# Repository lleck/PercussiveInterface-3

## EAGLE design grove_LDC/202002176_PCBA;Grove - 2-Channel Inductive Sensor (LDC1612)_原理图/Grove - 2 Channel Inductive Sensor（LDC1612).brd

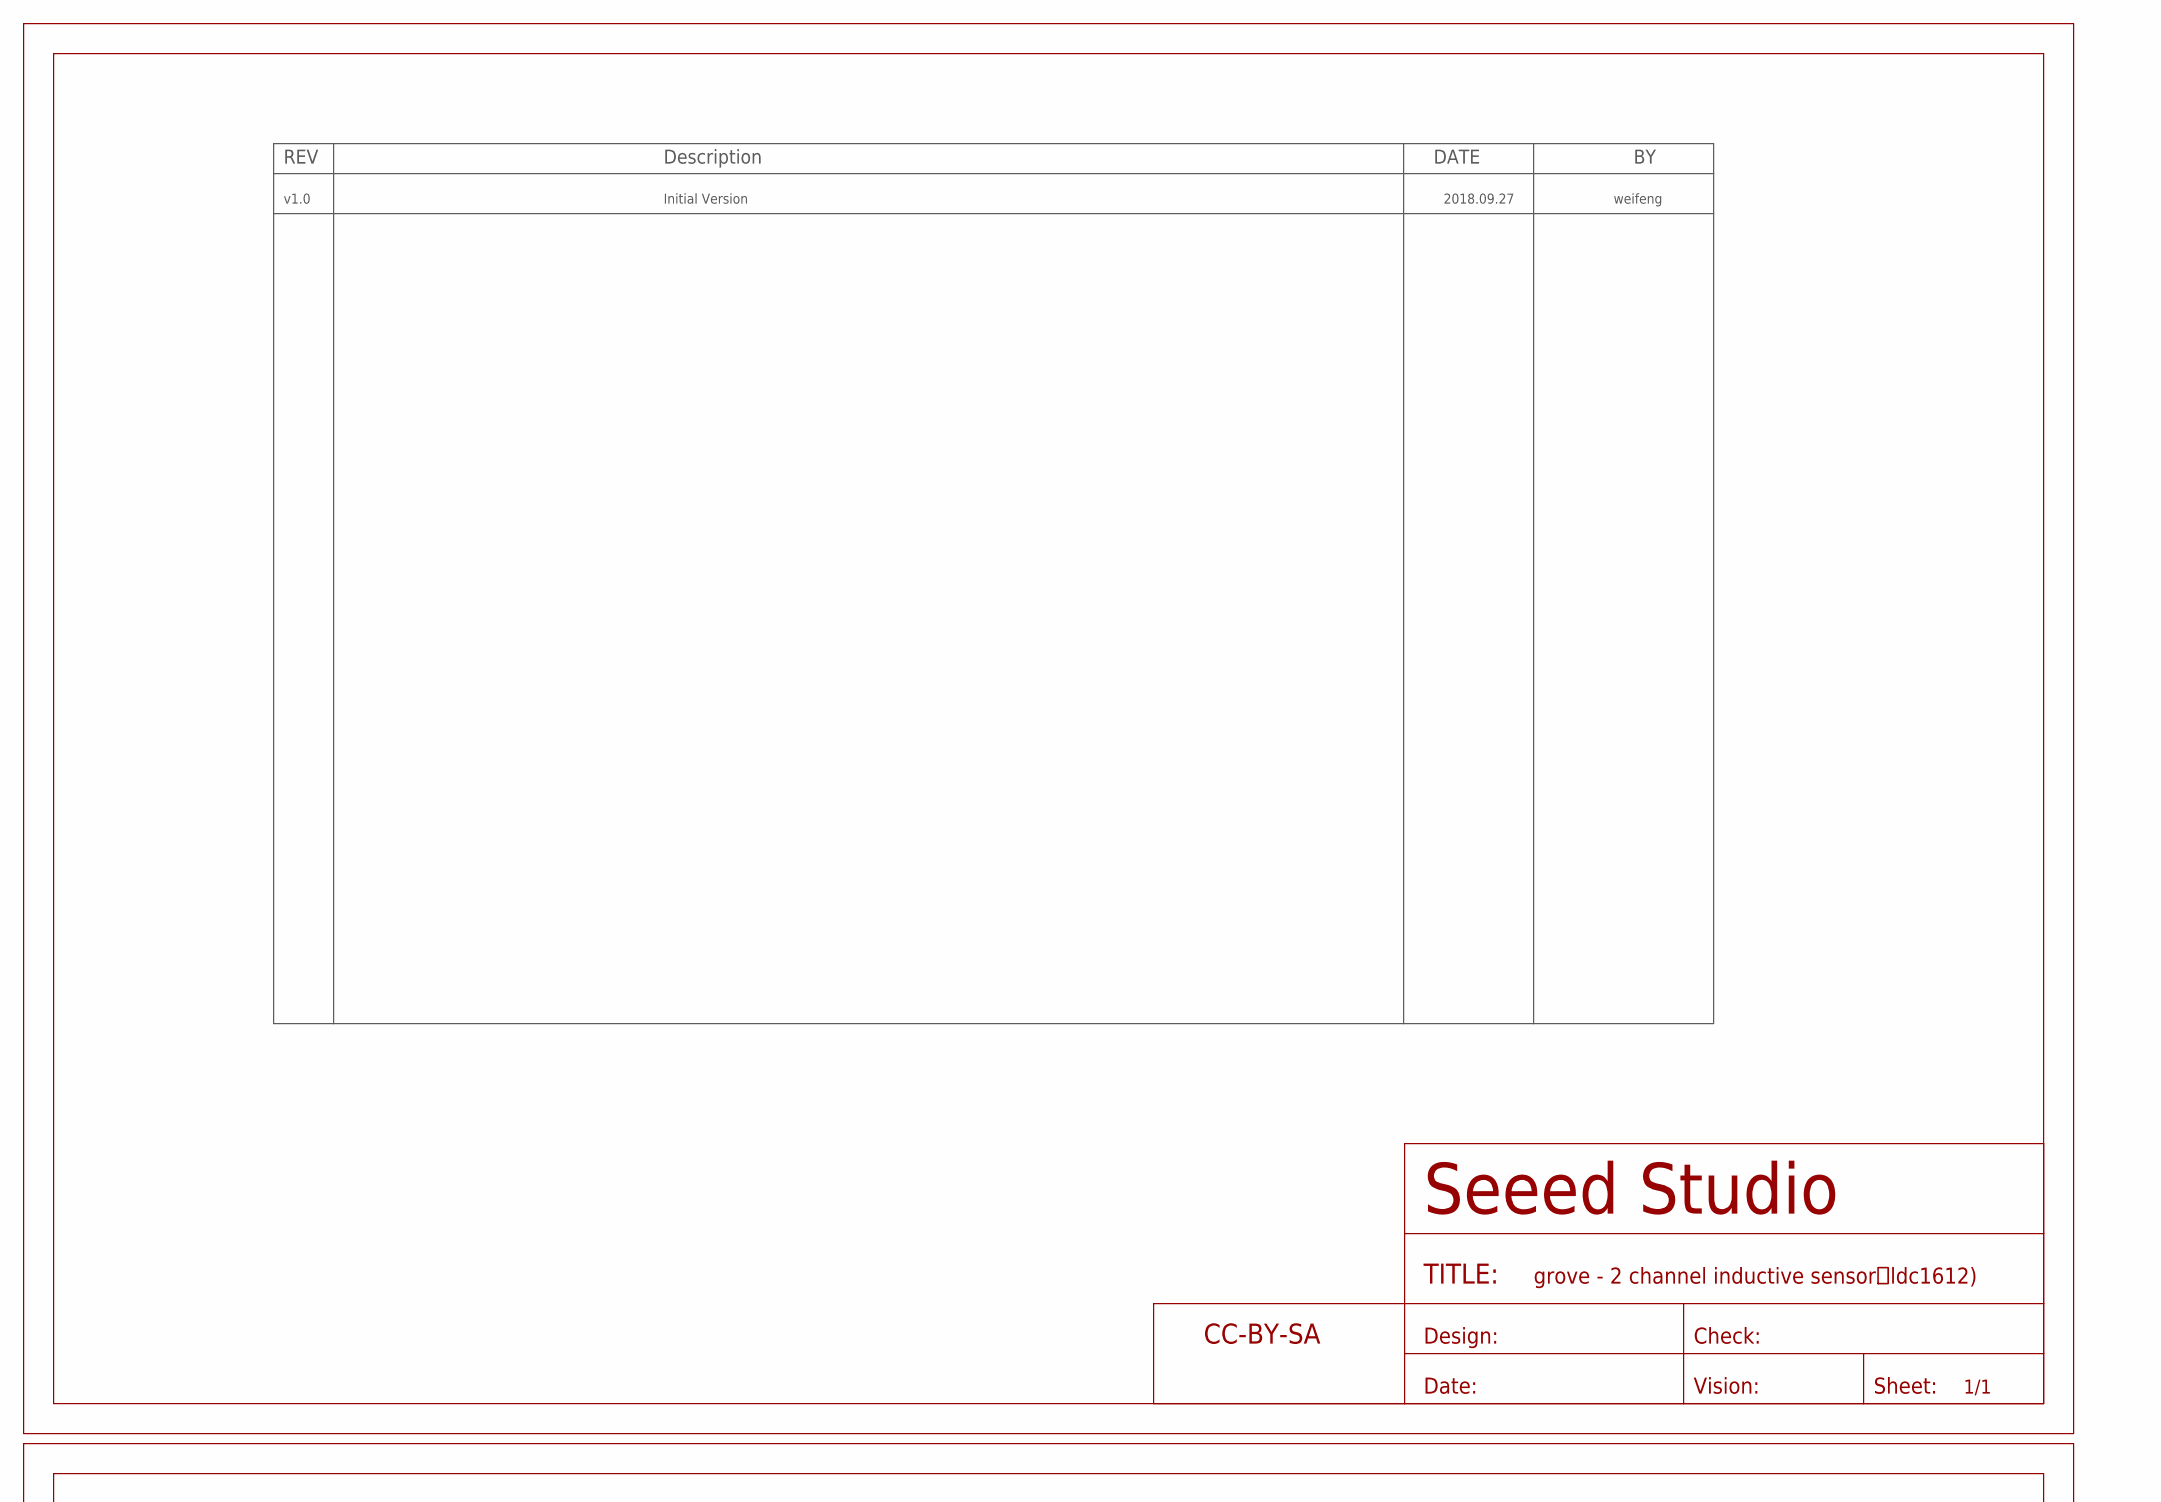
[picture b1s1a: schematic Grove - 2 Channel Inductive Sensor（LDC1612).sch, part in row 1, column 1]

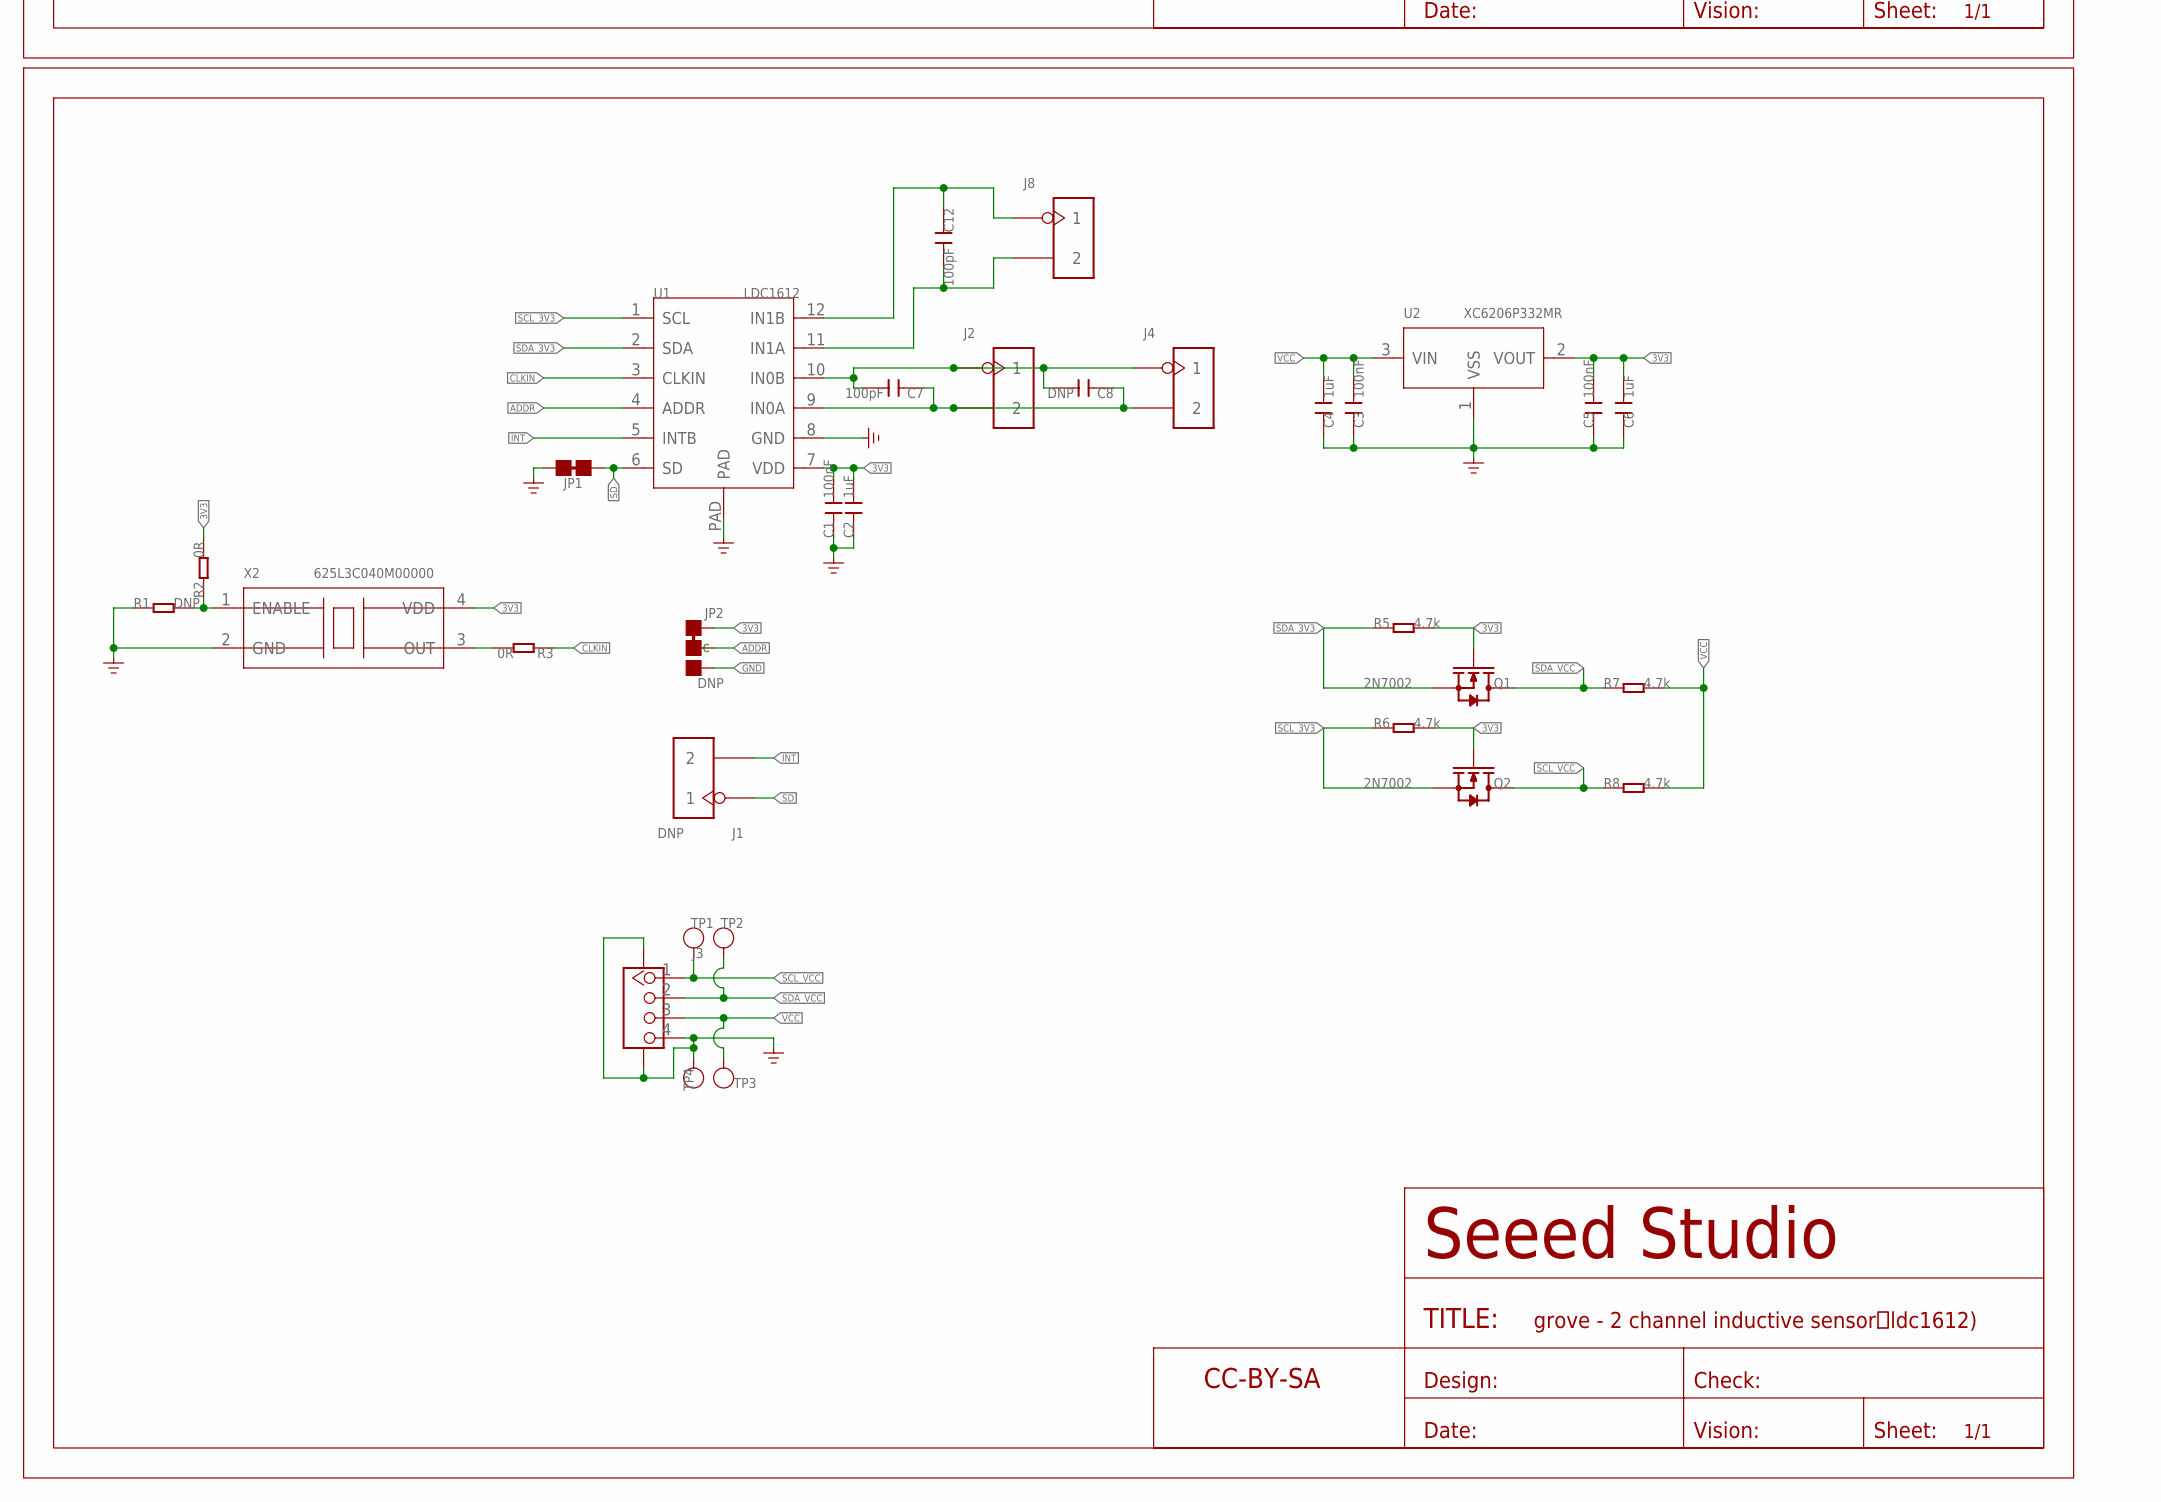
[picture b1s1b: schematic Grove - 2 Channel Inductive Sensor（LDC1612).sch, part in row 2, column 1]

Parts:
C1, C3, C5: 100nF; C0603
C2, C4, C6: 1uF; C0603
C7, C12: 100pF; C0603
C8: DNP; C0603
FR1: SEEEDSTUDIO-OPEN-SCH-FRAME; SEEEDSTUDIO-PCB-FRAME
J1: DNP; H2-2.54
J2, J4, J8: HEADER-2P-65/35MIL; H2-2.54
J3: GROVE-CONNECTOR-SMD'DD'; HW4-SMD-2.0
JP1: JP-2P-SHORT; 2P-SMD-SHORT
JP2: DNP; 3P-SMD-SHORT
Q1, Q2: 2N7002; SOT-23
R1: DNP; R0603
R2, R3: 0R; R0603
R5, R6, R7, R8: 4.7k; R0603
TP1, TP2, TP3, TP4: TEST-POINT'4545'; TP-D45MIL
U1: LDC1612; DFN12G-0.5-4X4MM
U2: XC6206P332MR; SOT-23
U$4: SEEEDSTUDIO-OPEN-SCH-FRAME; SEEEDSTUDIO-PCB-FRAME
X2: 625L3C040M00000; OSC4-SMD-2.5X2.0X0.8MM

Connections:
3V3: C1.2, C2.2, C5.2, C6.2, JP2.11 (L), Q1.1 (G), Q2.1 (G), R2.2, R5.2, R6.2, U1.7 (VDD), U2.2 (VOUT), X2.4 (VDD)
ADDR: JP2.MM (C), U1.4 (ADDR)
CLKIN: R3.1, U1.3 (CLKIN)
GND: C1.1, C2.1, C3.1, C4.1, C5.1, C6.1, J3.4, J3.SS1, J3.SS2, JP1.1, JP2.00 (R), R1.1, TP4.T, U1.8 (GND), U1.PAD, U2.1 (VSS), X2.2 (GND)
INT: J1.2, U1.5 (INTB)
unnamed: R3.2, X2.3 (OUT)
unnamed: R1.2, R2.1, X2.1 (ENABLE)
unnamed: C7.1, C8.1, J2.2, J4.2, U1.9 (IN0A)
unnamed: C7.2, C8.2, J2.1, J4.1, U1.10 (IN0B)
unnamed: C12.1, J8.1, U1.12 (IN1B)
unnamed: C12.2, J8.2, U1.11 (IN1A)
SCL_3V3: Q2.2 (S), R6.1, U1.1 (SCL)
SCL_VCC: J3.1, Q2.3 (D), R8.1, TP1.T
SD: J1.1, JP1.2, U1.6 (SD)
SDA_3V3: Q1.2 (S), R5.1, U1.2 (SDA)
SDA_VCC: J3.2, Q1.3 (D), R7.1, TP2.T
VCC: C3.2, C4.2, J3.3, R7.2, R8.2, TP3.T, U2.3 (VIN)

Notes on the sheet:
v1.0
Initial Version
2018.09.27
weifeng

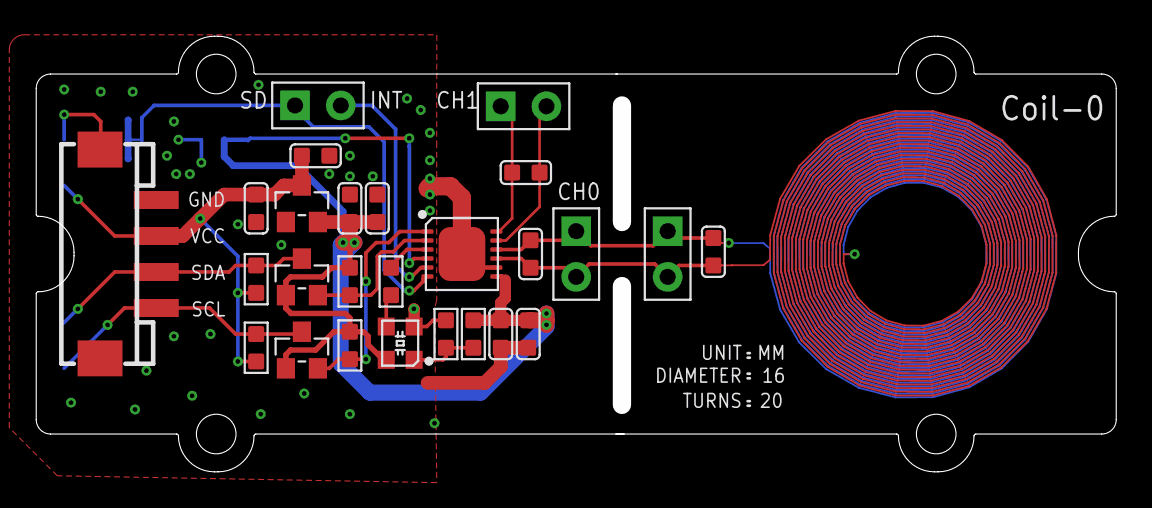
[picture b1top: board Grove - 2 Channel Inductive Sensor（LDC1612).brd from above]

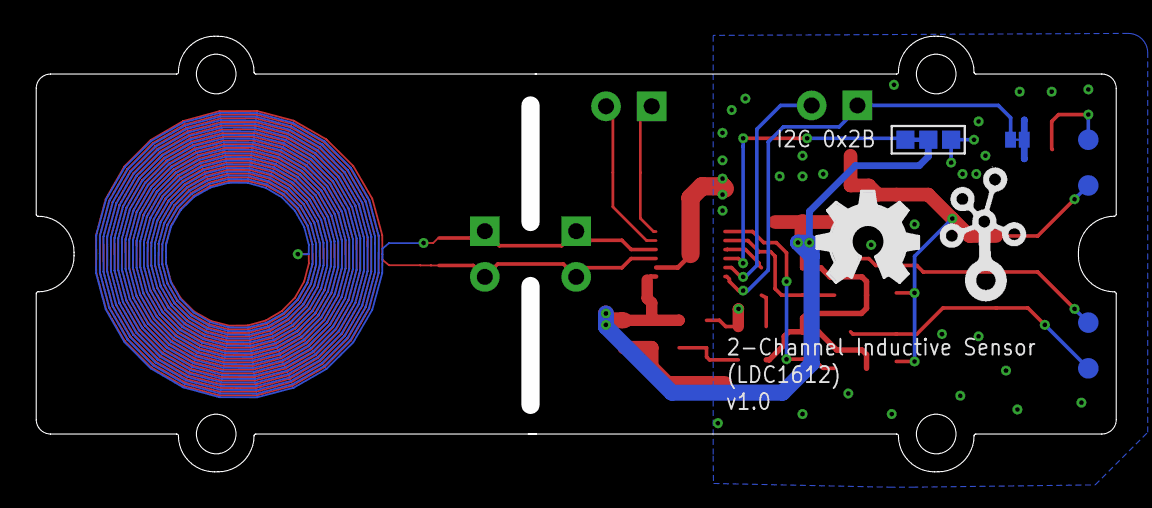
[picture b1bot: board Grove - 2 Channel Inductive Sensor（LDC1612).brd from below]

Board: 2 copper layers, 59.0 x 23.2 mm, 37 parts (8 on the bottom side), 17 nets.

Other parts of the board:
U$6: OSHW_FILLX200_NOTEXT
U$7: TWIGLOGO
U$14: GROVE-1*3-DRILL-DIM

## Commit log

2023-05-05 lleck
    first commit
2023-05-05 deleted
2023-05-05 rename3
2023-05-05 renaminggg
2023-05-09 conversion to 4layer
    inner ground and power layer and seperate outer layers for analog and
    digital signal routing
2023-05-09 folder structure
2023-05-09 small changes
2023-05-25 analog read 3 hall sens Arduino Code 1st
2023-05-27 notes
2023-05-29 more notes
2023-06-08 processing sketch
2023-06-14 backups
2023-06-19 processing
2023-06-29 differential reading of hall sensors
2023-06-30 dsfvadfv
2023-07-15 new layout 3.2
2023-07-15 layout 3.2
2023-07-15 nochmal update
2023-08-31 magnetometer array
2023-08-31 magnetometer arra<
2023-08-31 slightl<y new
2023-08-31 sdzhjrtghj
2023-09-20 stuff
2023-09-28 coil plugin etc
2023-10-08 new magnetoarray
2023-10-30 new arrray
2023-10-31 plentay stuffx
2023-11-03 many changes
2023-11-06 quadrillion changes
2023-11-09 almost there but not
2023-11-13 homework again
2023-11-14 almost ahgsngarsn
2023-11-15 jlc board
2023-11-15 jlc board ...
2023-11-16 bremen_workation
2023-11-19 full integrated with ti magnetometer
2023-11-21 afaeaefdga
2023-11-21 asgfebgsdfbas
2023-11-22 xgfbdbg
2023-11-23 yoyoyoyoy
2023-12-01 fgvjbhkljdtzrj
2023-12-05 before production / pinout ESP IO
2023-12-05 dfzvgh
2023-12-14 Code slowly layed out
2023-12-14 bla bla
2023-12-20 position readings
2023-12-20 chngs
2023-12-20 fastTrig und so
2023-12-22 trigger algo
2023-12-27 this & that
2023-12-28 bliblablub
2023-12-28 sevgfcs
2023-12-30 trblz
2023-12-30 rfrnz
2023-12-30 cghfjkvghf
2023-12-30 cdfvgh
2023-12-30 dfggsdfg
2024-01-04 456789
2024-01-04 5678654
2024-01-04 243636
2024-01-04 45735673456
2024-01-04 12341234
2024-01-07 sdfgdafg
2024-01-10 Logic Analyzer test SPI
2024-01-12 finaly reading all the sensors (uff)
2024-01-14 derfgsrtghsr
2024-02-03 240203 status quo
2024-02-03 restored from 01.02
2024-02-03 adfsghrewaet
2024-02-03 wrzetrte
2024-02-03 weghsdrfghsfgh
2024-02-03 wghsdrtghsrtg
2024-02-03 23452354
2024-02-03 346245673456
2024-02-03 240203_sechsuhr
2024-02-03 adfgadfg
2024-02-03 12341346345621345
2024-02-03 back to a working state
2024-02-04 fastled
2024-02-20 first 20.02.24
2024-02-20 readPosition(old)
2024-02-22 preKolloquium Commit

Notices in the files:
parts and their libraries:
moudle-new: This work is licensed under the Creative Commons Attribution 4.0 International License.
To view a copy of this license,visit:
http://creativecommons.org/licenses/by-sa/4.0
moudle-new: CC-BY-SA
